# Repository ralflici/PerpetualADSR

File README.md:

# Perpetual ADSR

This is a fully analog eurorack module that generates a looped envelope. After the attack and until the release, the module enters in a 2-state function bouncing between a high and a low value. The user can set the attack voltage, the central value and the time for each step to complete.  
This module works also without a `TRIGGER` signal since it can be generated from the `GATE`.

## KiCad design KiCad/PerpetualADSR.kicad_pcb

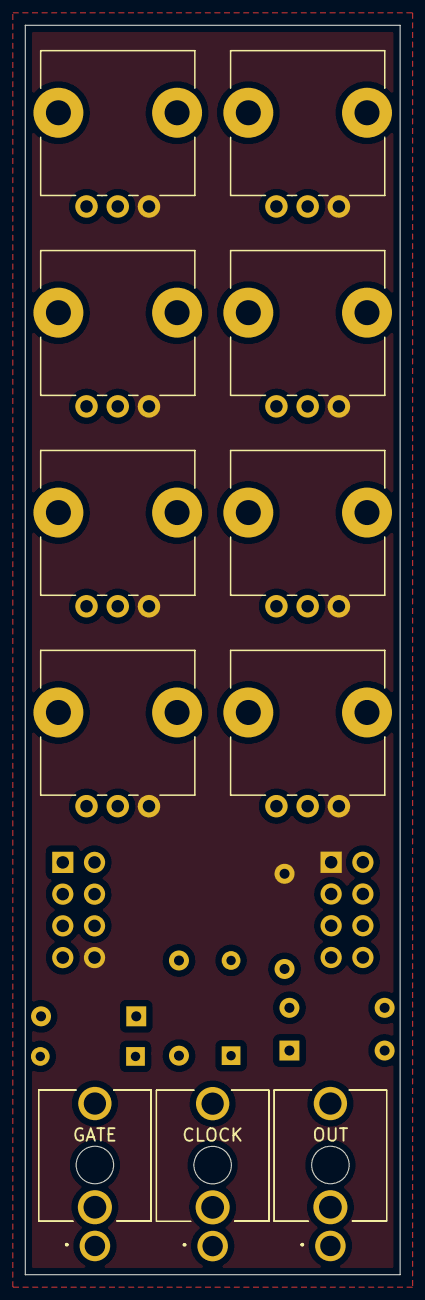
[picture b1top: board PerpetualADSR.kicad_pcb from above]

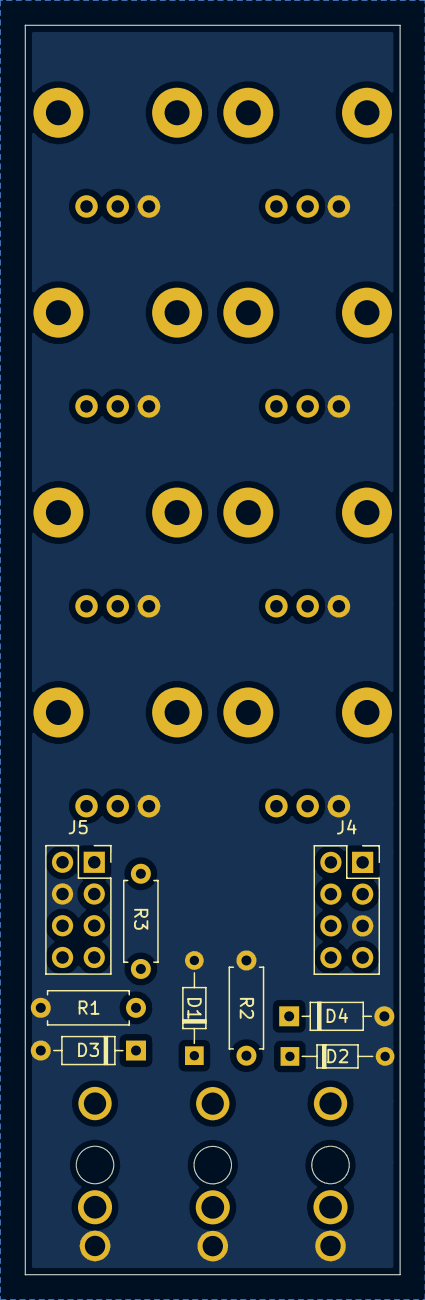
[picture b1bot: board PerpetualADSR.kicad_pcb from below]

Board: 2 copper layers, 30.0 x 100.0 mm, 20 parts (9 on the bottom side), 15 nets, no tracks yet.

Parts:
CLOCK: CLOCK; PJ301M
D1: S; D_DO-34_SOD68_P7.62mm_Horizontal
D2: Schottky; D_DO-34_SOD68_P7.62mm_Horizontal
D3, D4: 5.1V; D_DO-35_SOD27_P7.62mm_Horizontal
GATE: GATE; PJ301M
J4, J5: Conn_02x04_Counter_Clockwise; PinSocket_2x04_P2.54mm_Vertical
OUT: OUT; PJ301M
R1, R3: 10k; R_Axial_DIN0207_L6.3mm_D2.5mm_P7.62mm_Horizontal
R2: 100k; R_Axial_DIN0207_L6.3mm_D2.5mm_P7.62mm_Horizontal
RV1: REL_T; Potentiometer_Alps_RK09L_Single_Vertical
RV2: MAX_V; Potentiometer_Alps_RK09L_Single_Vertical
RV3: RISE_T; Potentiometer_Alps_RK09L_Single_Vertical
RV4: RISE_V; Potentiometer_Alps_RK09L_Single_Vertical
RV5: FALL_T; Potentiometer_Alps_RK09L_Single_Vertical
RV6: FALL_V; Potentiometer_Alps_RK09L_Single_Vertical
RV7: ATT_T; Potentiometer_Alps_RK09L_Single_Vertical
RV8: ATT_V; Potentiometer_Alps_RK09L_Single_Vertical

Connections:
+5V: J4.8, J5.1, R3.2, RV1.3, RV2.3, RV3.3, RV4.3, RV5.3, RV6.3, RV7.3, RV8.3
ATT_T: J4.1, RV7.2
ATT_V: J5.5, RV8.2
CLK: CLOCK.T, D1.1, D3.1, J4.6
FALL_T: J4.2, RV5.2
FALL_V: J5.6, RV6.2
GATE: D2.1, D4.1, GATE.T, J4.7
GND: CLOCK.S, D1.2, D2.2, D3.2, D4.2, GATE.S, J4.5, J5.4, OUT.S, R1.1, R2.1, RV1.1, RV2.1, RV3.1, RV4.1, RV5.1, RV6.1, RV7.1, RV8.1
MAX_V: J5.8, RV2.2
unnamed: GATE.TN, R2.2
unnamed: CLOCK.TN, R1.2, R3.1
OUT: J5.3, OUT.T
REL_T: J4.4, RV1.2
RISE_T: J4.3, RV3.2
RISE_V: J5.7, RV4.2

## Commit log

2021-03-19 trigger generated from gate
2021-03-19 added illustrator file
2021-03-19 added component names
2021-03-19 rearranged panel
2021-03-20 added GATE and TRIG jack inputs
2021-05-04 6hp version
2021-07-23 random commit
2021-08-11 minor updates
2021-12-12 started schematic
2021-12-13 added jacks for every pot
2021-12-15 schematics done
2021-12-18 starting PCB
2021-12-18 started PCB
